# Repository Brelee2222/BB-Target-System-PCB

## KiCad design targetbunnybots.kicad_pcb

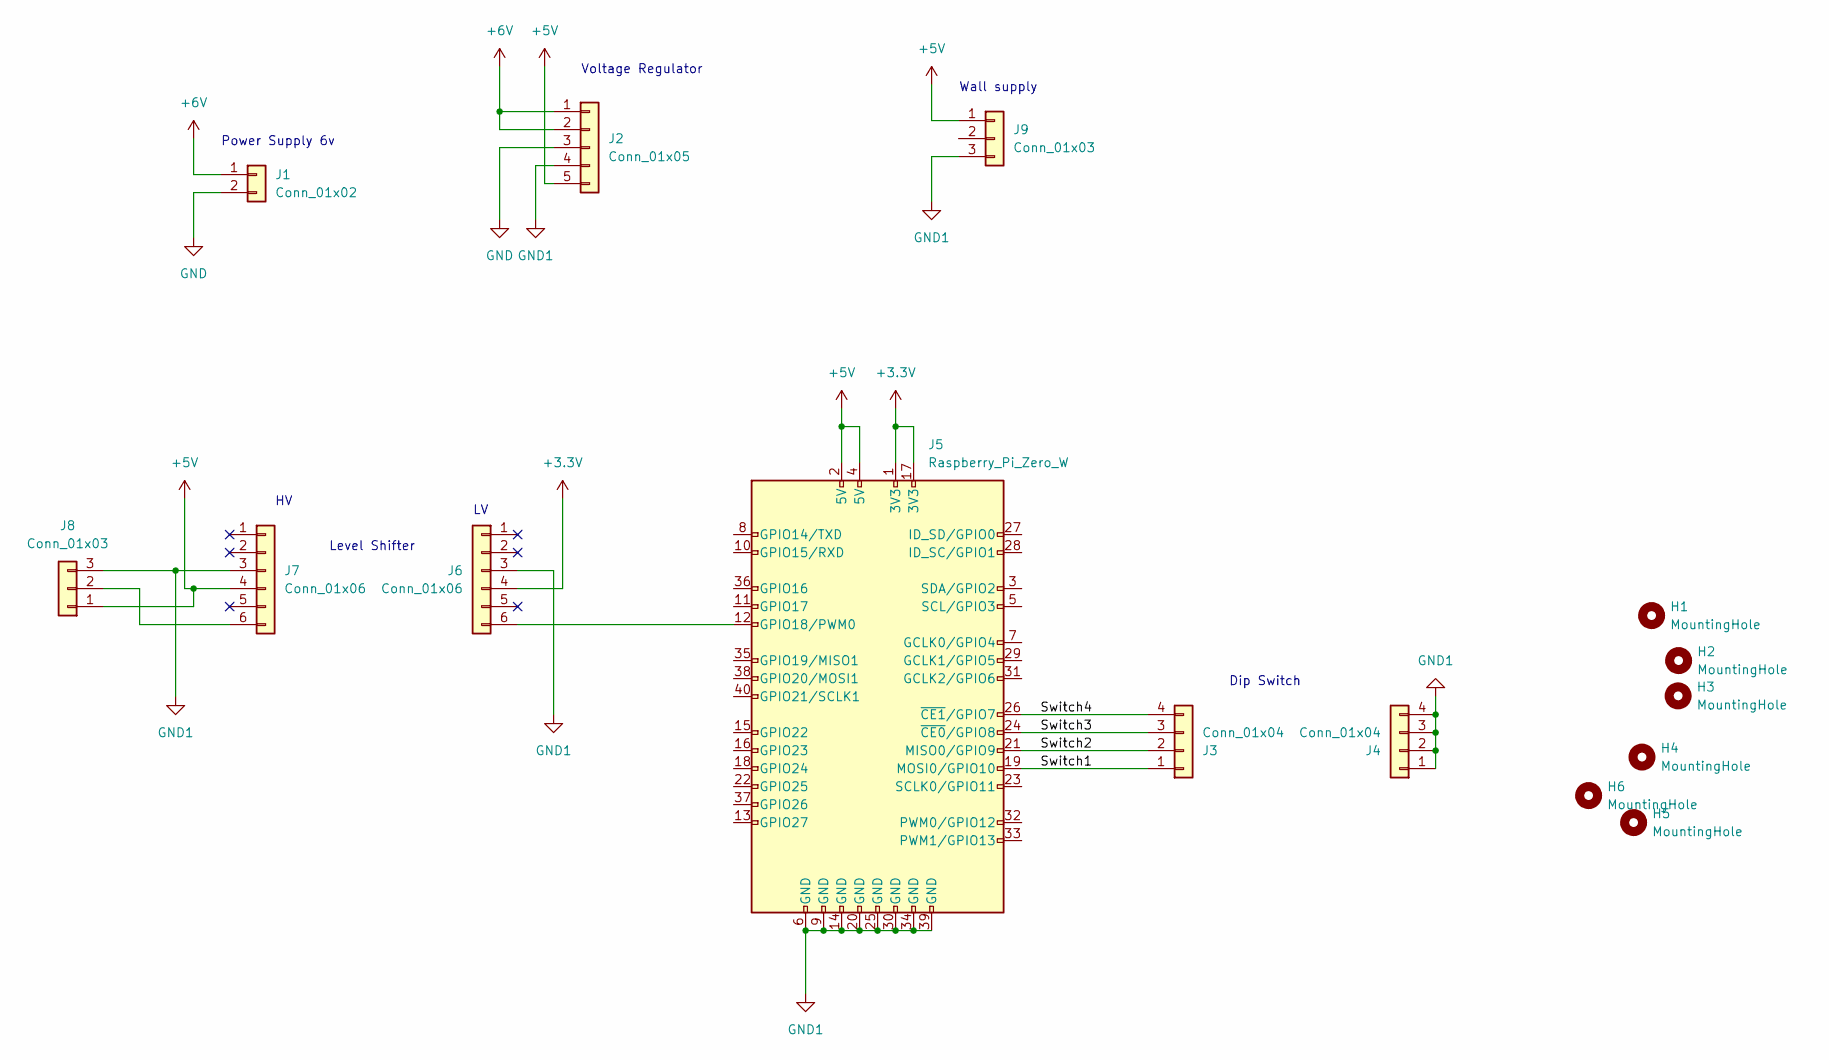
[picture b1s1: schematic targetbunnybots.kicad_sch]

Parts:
H1, H4: MountingHole; MountingHole_2.5mm
H2: MountingHole; MountingHole_4mm
H3, H5, H6: MountingHole; MountingHole_5mm
J1: Conn_01x02; PinHeader_1x02_P2.54mm_Vertical
J2: Conn_01x05; PinSocket_1x05_P2.54mm_Vertical
J3, J4: Conn_01x04; PinSocket_1x04_P2.54mm_Vertical
J5: Raspberry_Pi_Zero_W; PinSocket_2x20_P2.54mm_Vertical
J6, J7: Conn_01x06; PinSocket_1x06_P2.54mm_Vertical
J8, J9: Conn_01x03; PinHeader_1x03_P2.54mm_Vertical

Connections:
+3.3V: J5.1 (3V3), J5.17 (3V3), J6.4
+5V: J2.5, J5.2 (5V), J5.4 (5V), J7.4, J8.1, J9.1
+6V: J1.1, J2.1, J2.2
/Switch1: J3.1, J5.19 (MOSI0/GPIO10)
/Switch2: J3.2, J5.21 (MISO0/GPIO9)
/Switch3: J3.3, J5.24 (~CE0/GPIO8)
/Switch4: J3.4, J5.26 (~CE1/GPIO7)
GND: J1.2, J2.3
GND1: J2.4, J4.1, J4.2, J4.3, J4.4, J5.6 (GND), J5.9 (GND), J5.14 (GND), J5.20 (GND), J5.25 (GND), J5.30 (GND), J5.34 (GND), J5.39 (GND), J6.3, J7.3, J8.3, J9.3
unnamed: J5.12 (GPIO18/PWM0), J6.6
unnamed: J7.6, J8.2

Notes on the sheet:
Power Supply 6v
Voltage Regulator
Wall supply
Dip Switch
Level Shifter

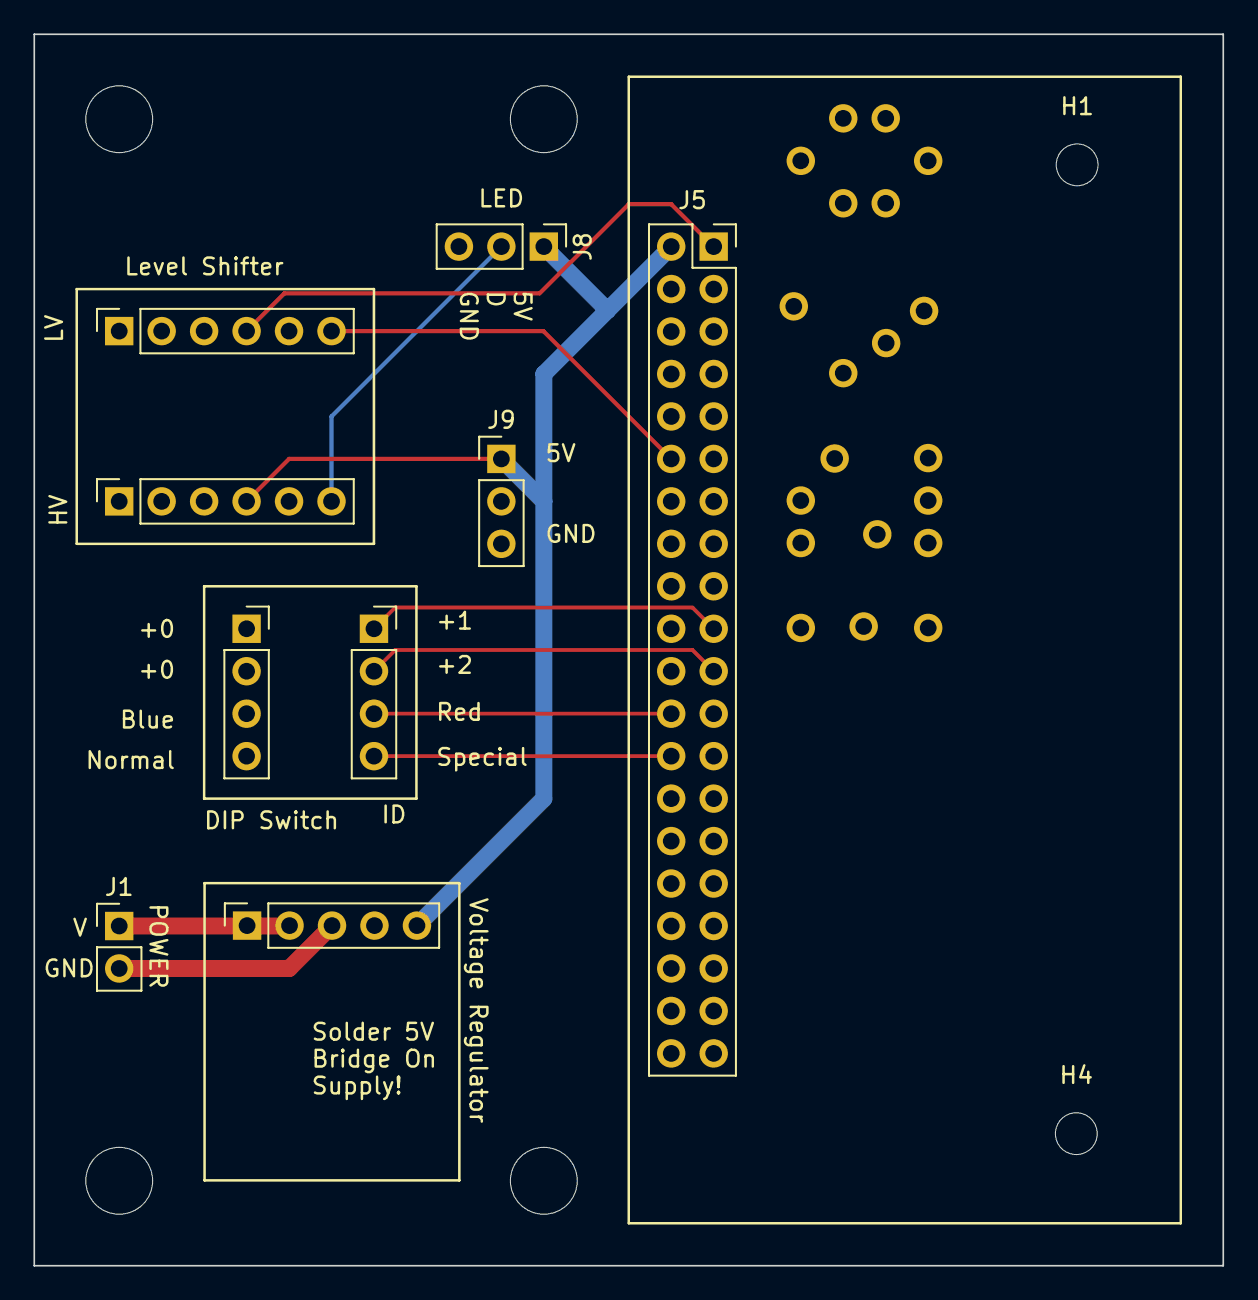
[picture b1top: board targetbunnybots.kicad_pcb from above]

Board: 2 copper layers, 71.1 x 73.7 mm, 15 parts (0 on the bottom side), 11 nets.
